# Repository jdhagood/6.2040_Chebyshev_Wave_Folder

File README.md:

\# 6.2040 Final Project: Chebyshev Wave Folder

It's gonna be dope

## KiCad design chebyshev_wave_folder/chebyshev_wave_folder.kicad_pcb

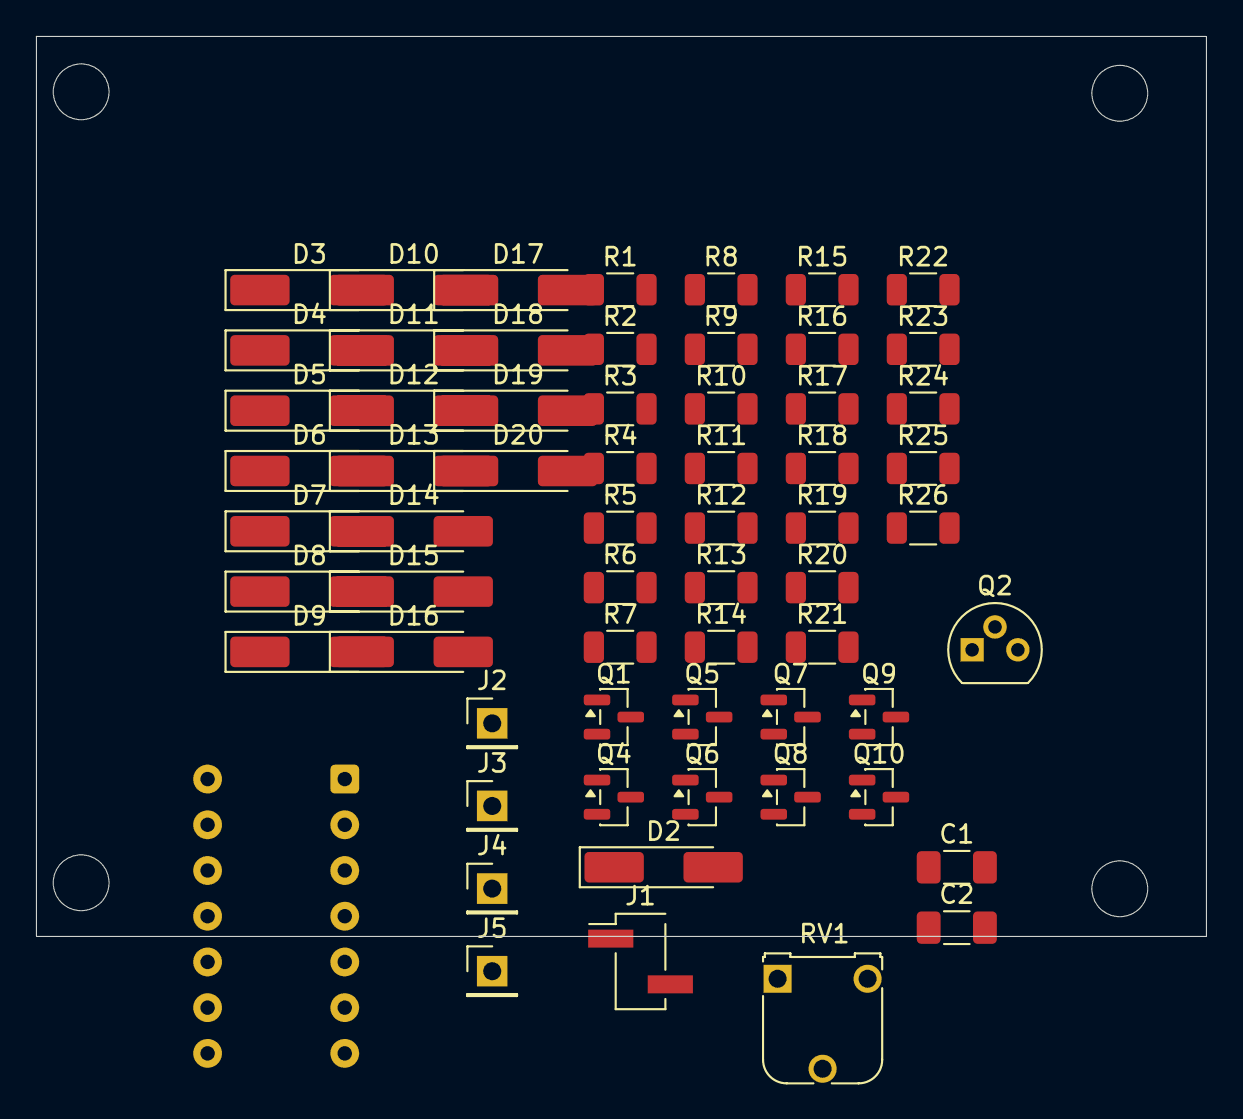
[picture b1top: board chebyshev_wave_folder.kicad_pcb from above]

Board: 2 copper layers, 65.0 x 50.0 mm, 63 parts (1 on the bottom side), 39 nets, no tracks yet.

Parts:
C1: 100u; C_1206_3216Metric_Pad1.33x1.80mm_HandSolder
C2: 100n; C_1206_3216Metric_Pad1.33x1.80mm_HandSolder
D2, D3, D4, D5, D6, D7, D8, D9, D10, D11, D12, D13, D14, D15, D16, D17, D18, D19, D20: 1N4148W; D_MiniMELF_Handsoldering
J1: Conn_01x02_Pin; PinHeader_1x02_P2.54mm_Vertical_SMD_Pin1Left
J2, J3, J4, J5: Conn_01x01_Pin; PinHeader_1x01_P2.54mm_Vertical
Q1, Q5, Q7, Q9: PNP; SOT-23
Q2: 2N5457; TO-92
Q4, Q6, Q8, Q10: NPN; SOT-23
R1, R2, R3, R4, R5, R6, R7, R8, R9, R10, R11, R12, R13, R14, R15, R16, R17, R18, R19, R20, R21, R22, R23, R24: 1K; R_1206_3216Metric
R25, R26: 10K; R_1206_3216Metric
RV1: R_Potentiometer; Potentiometer_Runtron_RM-065_Vertical
U1: TL074; DIP-14_W7.62mm

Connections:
4.5V: R18.2, R25.1, R26.2, U1.5 (+), U1.12 (+)
9V: C1.2, C2.2, J1.1, R8.1, R10.1, R13.1, R16.1, R25.2, U1.4 (V+)
/Vin: J5.1, U1.3 (+)
GND: C1.1, C2.1, J1.2, R7.2, R11.2, R14.2, R17.2, R26.1, U1.11 (V-)
unnamed: D2.2 (A), D3.2 (A), D5.1 (K), D7.1 (K), R2.1, U1.1, U1.2 (-)
unnamed: D2.1 (K), R3.1
unnamed: D3.1 (K), D4.2 (A)
unnamed: D4.1 (K), D6.2 (A), R2.2, R3.2, R4.2, RV1.1, RV1.2, U1.6 (-)
unnamed: D5.2 (A), D6.1 (K)
unnamed: D7.2 (A), R4.1
unnamed: D8.2 (A), Q1.2 (B)
unnamed: D8.1 (K), D9.2 (A), J2.1, R5.2, R6.1, U1.7
unnamed: D9.1 (K), Q4.2 (B)
unnamed: D10.2 (A), Q5.2 (B)
unnamed: D10.1 (K), D11.2 (A), Q1.1 (C), Q4.1 (C), R6.2, R9.1
unnamed: D11.1 (K), Q6.2 (B)
unnamed: D12.2 (A), Q7.2 (B)
unnamed: D12.1 (K), D13.2 (A), Q5.1 (C), Q6.1 (C), R9.2, R12.1
unnamed: D13.1 (K), Q8.2 (B)
unnamed: D14.2 (A), Q9.2 (B)
unnamed: D14.1 (K), D15.2 (A), Q7.1 (C), Q8.1 (C), R12.2, R15.1
unnamed: D15.1 (K), Q10.2 (B)
unnamed: D16.2 (A), D17.1 (K), D18.1 (K), R20.1, R21.1, R23.2, U1.13 (-)
unnamed: D16.1 (K), D19.2 (A)
unnamed: D17.2 (A), D20.1 (K)
unnamed: D18.2 (A), R22.1
unnamed: D19.1 (K), D20.2 (A), J4.1, R20.2, R21.2, R22.2, R24.1, U1.14
unnamed: J3.1, R19.2, R23.1, U1.8
unnamed: Q1.3 (E), R8.2
unnamed: Q4.3 (E), R7.1
unnamed: Q5.3 (E), R10.2
unnamed: Q6.3 (E), R11.1
unnamed: Q7.3 (E), R13.2
unnamed: Q8.3 (E), R14.1
unnamed: Q9.3 (E), R16.2
unnamed: Q9.1 (C), Q10.1 (C), R15.2, U1.10 (+)
unnamed: Q10.3 (E), R17.1
unnamed: R5.1, RV1.3
unnamed: R18.1, R19.1, U1.9 (-)

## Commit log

2026-04-03 jfet buffer added
2026-04-03 updated schematic
